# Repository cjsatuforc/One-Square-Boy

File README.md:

# One-Square-Boy
A one square inch control board for Teacup compatible 3D printers.

This project was created for the Return of the Square Inch Project on Hackaday.io.

Specs:
- ATmega328 microcontroller
- Four STSPIN220 low-voltage stepper motor drivers
- MJD122T4 MOSFET to control extruder temperature
- Power connectors for always-on fans 
- Connector for endstop signals
- Four layer board

To Do:
1. Receive board from OSHPark.
2. Populate.
3. Modify Teacup firmware to work with current setup, change pin definitions.
4. Gut Replikator Mini V1 and hook the new system up with 3D printed case and heatsinks.
5. Create video of print and complete submission for the competition.

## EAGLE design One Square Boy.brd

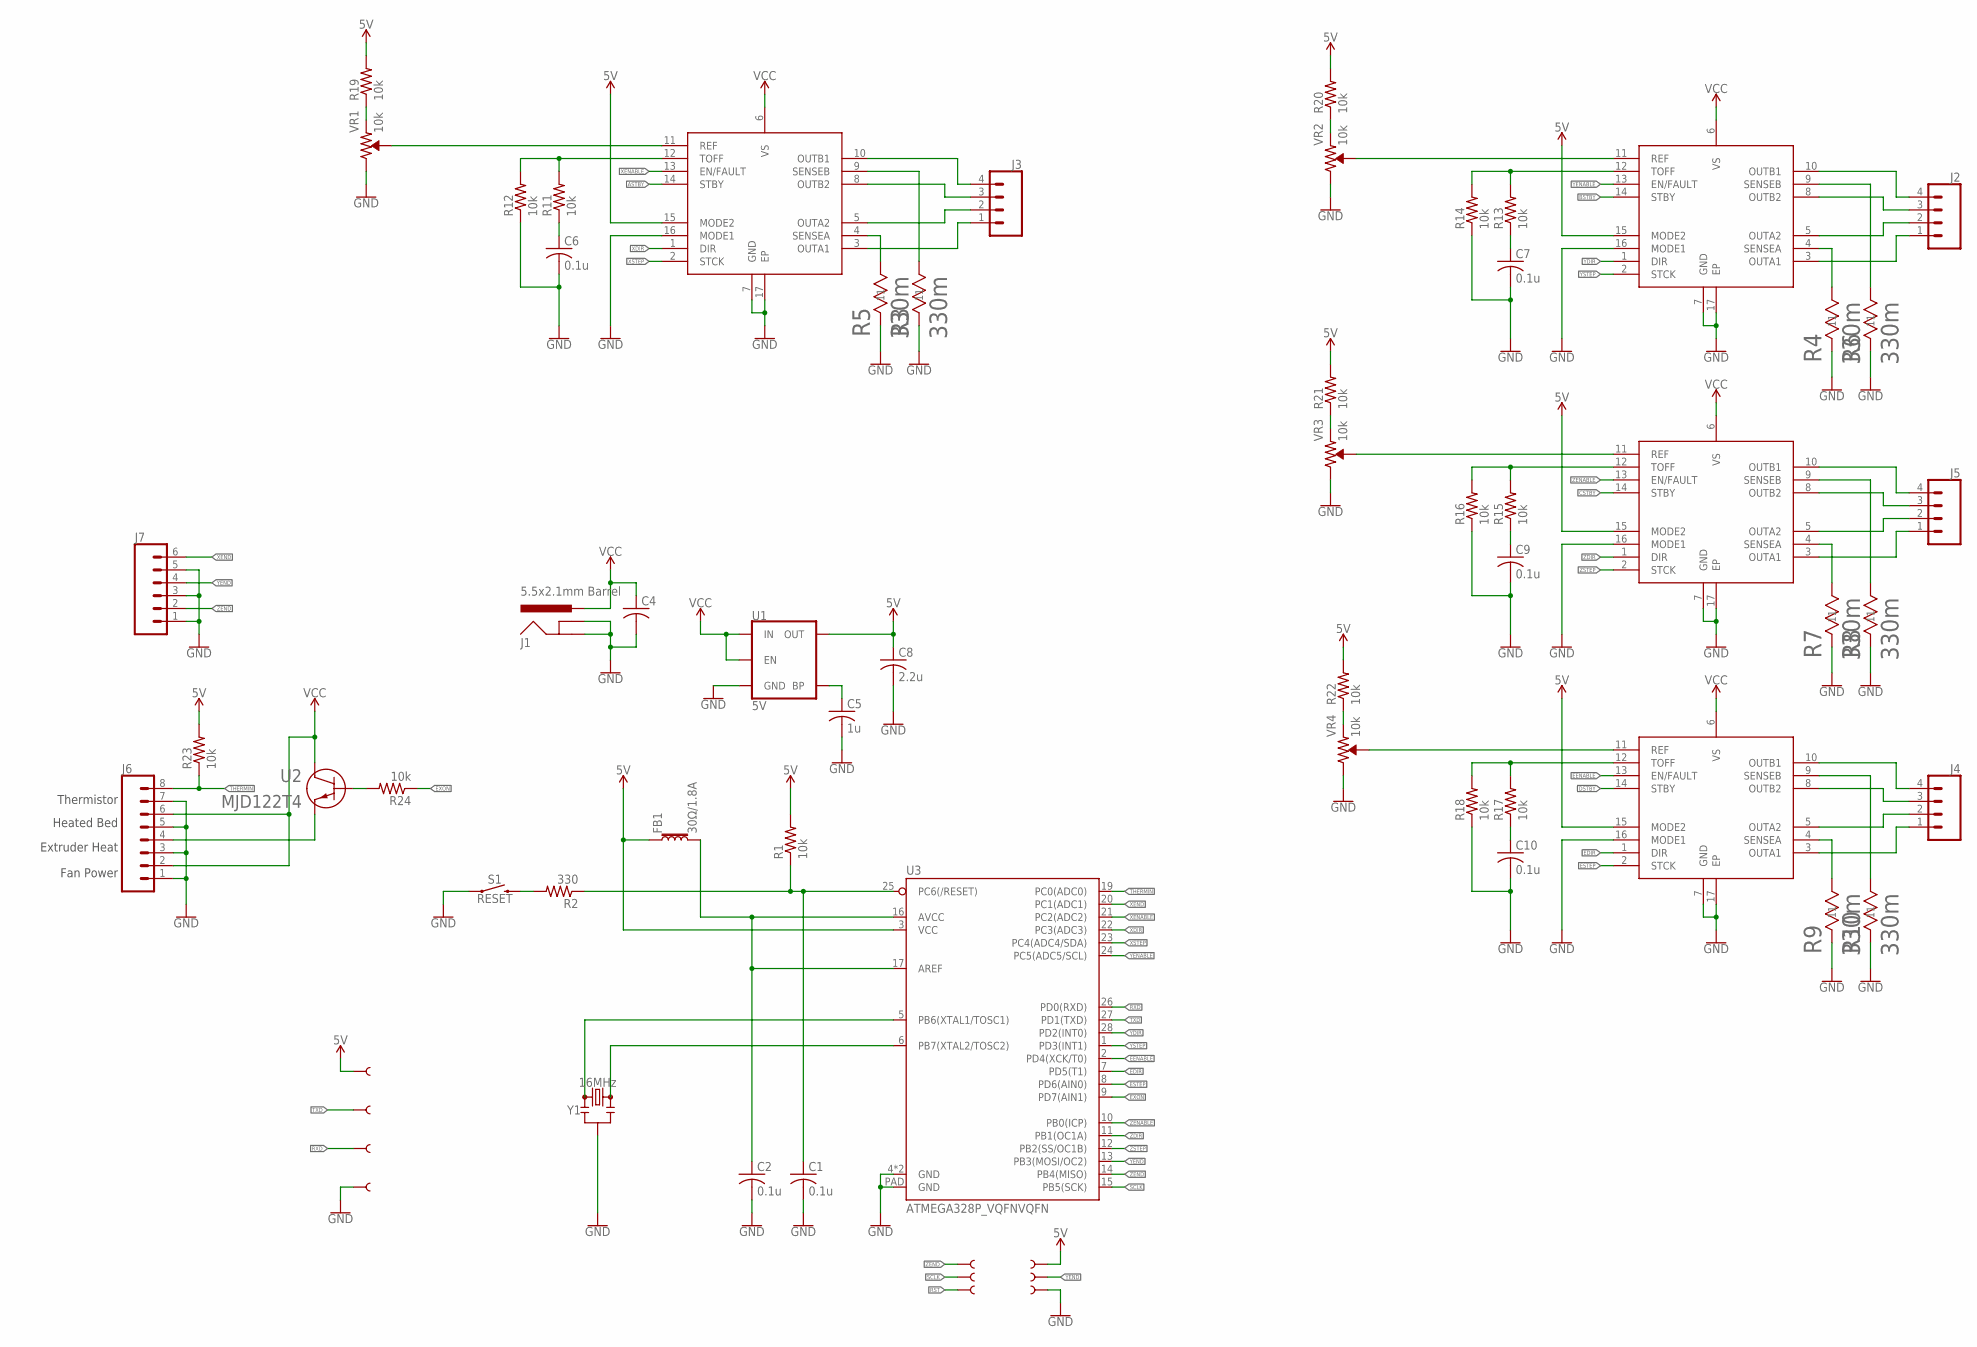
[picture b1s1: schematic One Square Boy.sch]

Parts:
C1, C2, C6, C7, C9, C10: 0.1u; C0402
C4: C-USC1206; C1206
C5: 1u; C0402
C8: 2.2u; C0402
FB1: 30Ω/1.8A; 0603
J1: 5.5x2.1mm Barrel; POWER_JACK_SMD
J2, J3, J4, J5: CONN_04SMD2; 1X04_1MM_RA
J6: CONN_08BM08B-SRSS-TB; BM08B-SRSS-TB
J7: CONN_06SMD-1MM; 1X06-1MM
R1, R11, R12, R13, R14, R15, R16, R17, R18, R19, R20, R21, R22, R23, R24: 10k; R0402
R2: 330; R0402
R3, R4, R5, R6, R7, R8, R9, R10: 330m; RES_2012-L
S1: RESET; TACTILE_SWITCH_SMD_4.6X2.8MM
TP1, TP2, TP3, TP4, TP5, TP6, TP7, TP8, TP9, TP10: TEST-POINT3X5; PAD.03X.05
U1: 5V; SOT23-5
U2: MJD122T4; DPAK
U3: ATMEGA328P_VQFNVQFN; VQFN-28
U$1, U$2, U$3, U$4: STSPIN220; QFN50P300X300X100-17N
VR1, VR2, VR3, VR4: 10k; TRIMPOT-SMD-TC33X
Y1: 16MHz; RESONATOR-SMD-3.2X1.3

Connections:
5V: C8.1, FB1.1, R1.2, R19.2, R20.2, R21.2, R22.2, R23.2, TP4.P$1, TP10.P$1, U1.5 (OUT), U3.3 (VCC), U$1.15 (MODE2), U$2.15 (MODE2), U$3.15 (MODE2), U$4.15 (MODE2)
ASTBY: U$1.14 (STBY)
AVCC: C2.1, FB1.2, U3.16 (AVCC), U3.17 (AREF)
BSTBY: U$2.14 (STBY)
CSTBY: U$3.14 (STBY)
DSTBY: U$4.14 (STBY)
EDIR: U3.7 (PD5(T1)), U$4.1 (DIR)
EENABLE: U3.2 (PD4(XCK/T0)), U$4.13 (EN/FAULT)
ESTEP: U3.8 (PD6(AIN0)), U$4.2 (STCK)
EXON: R24.1, U3.9 (PD7(AIN1))
GND: C1.2, C2.2, C4.2, C5.2, C6.2, C7.2, C8.2, C9.2, C10.2, J1.GND (GNDBREAK), J1.P$4 (GND), J6.1, J6.3, J6.5, J6.7, J7.1, J7.3, J7.5, R3.1 (11), R4.1 (11), R5.1 (11), R6.1 (11), R7.1 (11), R8.1 (11), R9.1 (11), R10.1 (11), R12.1, R14.1, R16.1, R18.1, S1.1, S1.2 (1), TP6.P$1, TP7.P$1, U1.2 (GND), U3.4 (GND), U3.18 (GND), U3.PAD (GND), U$1.7 (GND), U$1.16 (MODE1), U$1.17 (EP), U$2.7 (GND), U$2.16 (MODE1), U$2.17 (EP), U$3.7 (GND), U$3.16 (MODE1), U$3.17 (EP), U$4.7 (GND), U$4.16 (MODE1), U$4.17 (EP), VR1.1 (CW), VR2.1 (CW), VR3.1 (CW), VR4.1 (CW), Y1.2
unnamed: R2.2, S1.3 (2), S1.4 (2)
unnamed: U3.5 (PB6(XTAL1/TOSC1)), Y1.1
unnamed: U3.6 (PB7(XTAL2/TOSC2)), Y1.3
unnamed: J4.4, U$4.10 (OUTB1)
unnamed: J4.3, U$4.8 (OUTB2)
unnamed: J4.2, U$4.5 (OUTA2)
unnamed: J4.1, U$4.3 (OUTA1)
unnamed: J5.2, U$3.5 (OUTA2)
unnamed: J5.1, U$3.3 (OUTA1)
unnamed: J5.4, U$3.10 (OUTB1)
unnamed: J5.3, U$3.8 (OUTB2)
unnamed: J2.4, U$2.10 (OUTB1)
unnamed: J2.3, U$2.8 (OUTB2)
unnamed: J2.2, U$2.5 (OUTA2)
unnamed: J2.1, U$2.3 (OUTA1)
unnamed: J3.4, U$1.10 (OUTB1)
unnamed: J3.3, U$1.8 (OUTB2)
unnamed: J3.1, U$1.3 (OUTA1)
unnamed: J3.2, U$1.5 (OUTA2)
unnamed: R9.2 (22), U$4.4 (SENSEA)
unnamed: R10.2 (22), U$4.9 (SENSEB)
unnamed: R7.2 (22), U$3.4 (SENSEA)
unnamed: R8.2 (22), U$3.9 (SENSEB)
unnamed: R4.2 (22), U$2.4 (SENSEA)
unnamed: R6.2 (22), U$2.9 (SENSEB)
unnamed: R5.2 (22), U$1.4 (SENSEA)
unnamed: R3.2 (22), U$1.9 (SENSEB)
unnamed: C5.1, U1.4 (BP)
unnamed: R11.2, R12.2, U$1.12 (TOFF)
unnamed: C6.1, R11.1
unnamed: R13.2, R14.2, U$2.12 (TOFF)
unnamed: C7.1, R13.1
unnamed: R24.2, U2.1 (B1)
unnamed: R15.2, R16.2, U$3.12 (TOFF)
unnamed: C9.1, R15.1
unnamed: J6.4, U2.2 (E2)
unnamed: R17.2, R18.2, U$4.12 (TOFF)
unnamed: C10.1, R17.1
unnamed: R20.1, VR2.3 (CCW)
unnamed: U$4.11 (REF), VR4.2 (WIPER)
unnamed: U$3.11 (REF), VR3.2 (WIPER)
unnamed: U$2.11 (REF), VR2.2 (WIPER)
unnamed: U$1.11 (REF), VR1.2 (WIPER)
unnamed: R19.1, VR1.3 (CCW)
unnamed: R21.1, VR3.3 (CCW)
unnamed: R22.1, VR4.3 (CCW)
RST: C1.1, R1.1, R2.1, TP3.P$1, U3.25 (PC6(/RESET))
RXD: TP8.P$1, U3.26 (PD0(RXD))
SCLK: TP2.P$1, U3.15 (PB5(SCK))
THERMIN: J6.8, R23.1, U3.19 (PC0(ADC0))
TXD: TP9.P$1, U3.27 (PD1(TXD))
VCC: C4.1, J1.VIN0 (PWR), J6.2, J6.6, U1.1 (IN), U1.3 (EN), U2.3 (C3), U$1.6 (VS), U$2.6 (VS), U$3.6 (VS), U$4.6 (VS)
XDIR: U3.22 (PC3(ADC3)), U$1.1 (DIR)
XENABLE: U3.21 (PC2(ADC2)), U$1.13 (EN/FAULT)
XEND: J7.6, U3.20 (PC1(ADC1))
XSTEP: U3.23 (PC4(ADC4/SDA)), U$1.2 (STCK)
YDIR: U3.28 (PD2(INT0)), U$2.1 (DIR)
YENABLE: U3.24 (PC5(ADC5/SCL)), U$2.13 (EN/FAULT)
YEND: J7.4, TP5.P$1, U3.13 (PB3(MOSI/OC2))
YSTEP: U3.1 (PD3(INT1)), U$2.2 (STCK)
ZDIR: U3.11 (PB1(OC1A)), U$3.1 (DIR)
ZENABLE: U3.10 (PB0(ICP)), U$3.13 (EN/FAULT)
ZEND: J7.2, TP1.P$1, U3.14 (PB4(MISO))
ZSTEP: U3.12 (PB2(SS/OC1B)), U$3.2 (STCK)

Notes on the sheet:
Thermistor
Heated Bed
Extruder Heat
Fan Power

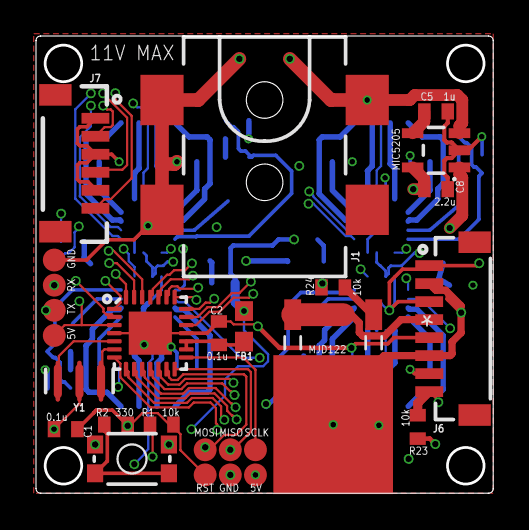
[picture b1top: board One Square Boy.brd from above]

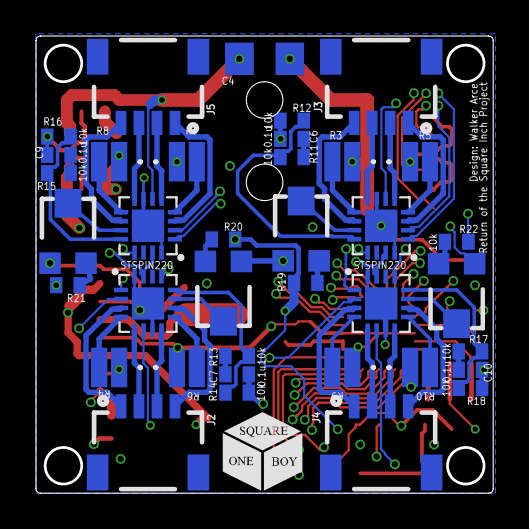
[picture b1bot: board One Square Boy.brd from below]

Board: 4 copper layers, 25.4 x 25.4 mm, 64 parts (37 on the bottom side), 71 nets.

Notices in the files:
parts and their libraries:
SparkFun-Coils: Licensing: Creative Commons ShareAlike 4.0 International - https://creativecommons.org/licenses/by-sa/4.0
PatternAgents-Beautify: License : http://creativecommons.org/licenses/by-sa/3.0
(Creative Commons 3.0)
